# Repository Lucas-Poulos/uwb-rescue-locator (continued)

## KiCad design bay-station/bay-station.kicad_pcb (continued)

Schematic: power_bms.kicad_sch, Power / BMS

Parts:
BT1: 3.7V Li-Ion (JST-PH pigtail); JST_PH_S2B-PH-K_1x02_P2.00mm_Horizontal
C1: 10uF; C_0603_1608Metric
C2, C3: 4.7uF; C_0603_1608Metric
C4: 0.1uF; C_0603_1608Metric
D1: MBRA140T3G; D_SMA
D2, D3: ESD5B5.0ST1G; D_SOD-523
J1: CUI PJ-063AH; BarrelJack_CUI_PJ-063AH_Horizontal
J2: USB4125-GF-A; USB_C_Receptacle_GCT_USB4125-xx-x_6P_TopMnt_Horizontal
Q1: AO3401A; SOT-23
R1: 100k; R_0603_1608Metric
R2: 2.00k; R_0603_1608Metric
R3: 20.0k; R_0603_1608Metric
R4: 330k; R_0603_1608Metric
R5: 110k; R_0603_1608Metric
R6, R7: 5.1k; R_0603_1608Metric
TH1: 10k NTC; R_0603_1608Metric
TP415: VBATT_PROT; TestPoint_Pad_D1.0mm
TP416: THERM; TestPoint_Pad_D1.0mm
TP417: BATT_RAW; TestPoint_Pad_D1.0mm
U1: MCP73871; QFN-20-1EP_4x4mm_P0.5mm_EP2.5x2.5mm
U2: MAX17048G+T10; MAX17048_TDFN8-EP_PLACEHOLDER

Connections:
+5V_IN: C1.1, D1.1 (K), D2.1 (A1), J2.A9 (VBUS), J2.B9 (VBUS), R4.1, U1.3 (SEL), U1.9 (~TE), U1.17 (CE), U1.18 (IN), U1.19 (IN); also elsewhere on the board
+VSYS: C2.1, U1.1 (OUT), U1.20 (OUT); also elsewhere on the board
BARREL_VIN: D1.2 (A), J1.1
BATT_FET_GATE: Q1.1 (G), R1.1
BATT_RAW: BT1.1 (+), Q1.2 (S), TP417.1 (1_1)
CC1: J2.A5 (CC1), R6.1
CC2: J2.B5 (CC2), R7.1
FG_ALRT: U2.5 (~ALRT); also elsewhere on the board
GND: BT1.2 (-), C1.2, C2.2, C3.2, C4.2, D2.2 (A2), D3.2 (A2), J1.2, J2.A12 (GND), J2.B12 (GND), J2.S1 (SHIELD), R1.2, R2.2, R3.2, R5.2, R6.2, R7.2, TH1.2, U1.4 (PROG2), U1.10 (V_{SS}), U1.11 (V_{SS}), U1.21 (V_{SS}), U2.1 (CTG), U2.4 (GND), U2.6 (QSTRT), U2.9 (GND); also elsewhere on the board
I2C_SCL: U2.7 (SCL); also elsewhere on the board
I2C_SDA: U2.8 (SDA); also elsewhere on the board
PROG1: R2.1, U1.13 (PROG1)
PROG3: R3.1, U1.12 (PROG3)
THERM: TH1.1, TP416.1 (1_1), U1.5 (THERM)
VBATT_PROT: C3.1, C4.1, D3.1 (A1), Q1.3 (D), TP415.1 (1_1), U1.14 (V_{BAT}), U1.15 (V_{BAT}), U1.16 (V_{BAT_SENSE}), U2.3 (VDD)
VPCC: R4.2, R5.1, U1.2 (VPCC)
nPG: U1.6 (~PG); also elsewhere on the board
nSTAT1_LBO: U1.8 (STAT1/~LBO); also elsewhere on the board
nSTAT2: U1.7 (STAT2); also elsewhere on the board

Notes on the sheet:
Test pads TP415-TP417 (TP414 +5V_IN deleted 2026-11-18: duplicate of TP104) and the THERM window (2026-11-17, power agent) TH1 sizing, MCP73871 DS20002090E Sec 1.0: ITHERM 47/50/53 uA, VT1 1.20/1.24/1.26 V, VT2 0.23/0.25/0.27 V. Charging is suspended when R_NTC > VT1/ITHERM = 22.6-26.8k (cold) or <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

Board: 4 copper layers, 360 parts (0 on the bottom side), 207 nets, no tracks yet.

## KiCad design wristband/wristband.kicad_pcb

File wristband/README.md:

# Wristband

The worn tag. Open `wristband.kicad_pro` in KiCad.

## Scope

Deliberately minimal: **battery management plus one UWB module, and not much
else.** The tag's only job is to take part in a two-way ranging exchange with
the bay station's center anchor. Everything not needed for that is gone.

- **UWB + MCU**: Qorvo **DWM3001C** (resolved 2026-09-19) -- one module
  containing the DW3110 UWB transceiver, a Nordic nRF52833 MCU, an ST
  LIS2DH12 accelerometer, the UWB and Bluetooth antennas, power management
  and the 38.4 MHz crystal. Its datasheet states it *"requires no RF design
  as the antenna and associated analog and RF components are on the module"*.
- **BLE and the accelerometer are unused.** The tag talks only over UWB. Both
  are silicon inside a module bought for its Cortex-M4 and its UWB radio --
  they cost nothing to leave idle: no external parts, no wiring, no firmware.
  See "Worth revisiting" below.
- **BMS**: sized for "just enough" runtime -- size and weight take priority
  over battery life here, in contrast with the bay station.

Why the tag transmits once per fix: the bay station's center anchor completes
the ranging exchange, and the three outer anchors timestamp that *same*
transmission. One transmission, four measurements -- deliberately, because
the tag is the power-constrained side. See `../docs/positioning.md`.

## Status

Seven hierarchical sheets, all registered in `wristband.kicad_pro`'s `sheets`
list and wired into `wristband.kicad_sch` as sheet symbols.

| Sheet | Status | Contents |
|---|---|---|
| `power_bms` | **Wired** (global labels, no drawn wires), ERC clean | Full battery/charging/protection chain |
| `radio_mcu` | **Wired**, ERC clean | DWM3001C (U4) + decoupling; SWD, RESET_N, SWO, VBAT_SENSE, SOS button, LED_SYS, FW_MARKER |
| `regulation` | **Wired**, ERC clean | TPS7A0233PDBVR LDO -> 3.3V (U5) |
| `programming_debug` | **Wired**, ERC clean | ARM Cortex Debug SWD header |
| `indicators` | **Wired** (global labels + short wires), ERC clean | System LED D4/R13 on P0.14. Charge LED is D2/R10 on `power_bms` |
| `testpoints` | **Wired** (global labels, no drawn wires), ERC clean | TP1-TP5: +3V3, VBAT, 2x GND, FW_MARKER |
| `mechanical` | No wiring needed | 4x M2 mounting holes |

**Every sheet that has nets is now wired.** `mechanical` carries only
mounting holes and needs no nets. `indicators` and `testpoints` were the last
two placement-only sheets (wired 2026-11-18); they used to account for all 13
of the board's `pin_not_connected` ERC errors.

**ERC, re-run 2026-11-18 with kicad-cli 10.0.5 on `wristband.kicad_sch`
(full hierarchy, 39 BOM lines): 2 violations, 0 errors**, both
`lib_symbol_mismatch` warnings from the embedded 8.0-format symbol copies
differing from the 10.x libraries (pre-existing and by design -- see the
flattened-copy workaround in `../CLAUDE.md`). Before: 16 (13 errors).
Per-sheet ERC of a single child sheet shows spurious `isolated_pin_label` /
`power_pin_not_driven` items because the other end of each global label is on
another sheet; run ERC on the root.

**Reference-designator collision fixed 2026-11-18.** `indicators` had its own
`D2`/`R10`/`D3`/`R11`, colliding with `power_bms` (D2 + R10 are the charge LED,
D3 is the VBUS TVS) and `radio_mcu` (R11 is a battery-sense divider resistor);
the BOM export was merging them into rows like `D3 "ESD5B5.0ST1G,LED"`. The
duplicate charge-LED pair was deleted from `indicators` and the system LED
renumbered `D4`/`R13`. The PCB has not been updated from the schematic: it
holds no footprints for `D4`, `R13` or `TP1`-`TP5` yet.

**DRC, re-run 2026-11-06: 210 violations.** This line also used to say "one
violation, `invalid_outline`, because no board outline is drawn yet" --
stale since PR #5 landed the actual PCB (36 footprints, a real outline).
Current breakdown: 100 unconnected_items (the unrouted ratsnest -- expected,
nothing is routed yet), 91 silk_over_copper, 71 silk_overlap, 33
via_dangling, 10 copper_edge_clearance, 3 silk_edge_clearance, 2 clearance.
The silk_over_copper/silk_overlap counts jumped from 57/7 on 2026-11-06 when
every footprint's Value was moved from hidden-on-F.Fab to visible on
F.SilkS (see `docs/decisions.md`) -- expected and accepted: 0402/0603
passive values often don't fit silkscreen cleanly, and resolving the
overlaps is layout work, not a reason to hide the values again.

### Sheet detail

- **`power_bms.kicad_sch`** -- the complete battery chain: 2-pin JST-PH
  battery input (`BT1`); AO3401A P-MOSFET reverse-polarity "ideal diode"
  (`Q1`, `R1`); battery-rail TVS ESD5B5.0ST1G (`D1`); DW01A + FS8205A
  single-cell overcharge/overdischarge/overcurrent protection wired per
  Fortune Semiconductor's own DW01A typical application circuit (`U1`, `Q2`,
  `R2`, `R3`, `C1`); MCP73831 Li-Po charger with power-only USB-C input, PROG
  resistor sized for ~147mA charge current, and datasheet-recommended
  input/output caps (`U2`, `J1`, `R4`, `C2`, `C3`, `R5`, `R6`); bulk/bypass
  decoupling on the protected `VBAT` rail (`C4`, `C5`).

  Net identity is carried entirely by global labels placed on top of each
  pin. ERC: 0 errors, 1 harmless documented warning. Full rationale in
  `power_bms_notes.md`.

- **`radio_mcu.kicad_sch`** -- one `wristband:DWM3001C` (`U4`) plus VDD
  decoupling (`C6` 100nF, `C7` 10uF). Now wired: SWD (`SWDCLK`/`SWDIO`/
  `SWO`), `RESET_N`, `VBAT_SENSE` on P0.02/AIN0, the SOS button on
  P0.17, `LED_SYS` on P0.14 and `FW_MARKER` on P0.22. 14 of the module's 48 pins are tied (adding `LED_SYS` on P0.14 and `FW_MARKER` on P0.22); the rest await the pin
  assignments still open in `../docs/decisions.md`.

  Pin data verified against the real Qorvo DWM3001C Data Sheet Rev B (May
  2022), Table 2. One caveat carried in the symbol: **pin 18 is not
  documented in that table** (it lists 1-17 and 19-48), so it is modelled as
  a passive NC and needs confirming against the land-pattern figure.

  Decoupling values are conservative standard practice, *not*
  datasheet-specified -- the module has on-board power management and Qorvo
  publishes no external application circuit for it.

  Two real layout requirements are recorded in the sheet's own notes: the
  **10 mm antenna keep-out** (Section 7.1) and **keeping the module at least
  1 cm from the PCB edge** (Section 7.2), which reduces the horizontally
  polarized radiation component and improves multipath resilience.

- **`regulation.kicad_sch`** -- TI **TPS7A0233PDBVR** LDO (`U5`, SOT-23-5,
  3.3V fixed, 200mA, 25nA typ Iq) steps the protected `VBAT` rail (up to
  4.2V at full charge) down to `+3V3`. Replaced the MCP1700T-3302E/TT on
  2026-09-23, whose 1.6uA Iq had become the board's largest standby draw --
  see `../docs/decisions.md`. Still required: the DWM3001C's operating
  maximum is 3.6V (Table 4), well under a full battery. **EN must be tied
  high**; the part is disabled when EN floats. See `regulation_notes.md`.

- **`programming_debug.kicad_sch`** -- ARM Cortex Debug SWD connector (`J3`,
  `Connector:Conn_ARM_JTAG_SWD_10`, 2x5 1.27mm). Now targets the nRF52833
  inside U4, via `SWD_CLK` (pin 2) and `SWD_DIO` (pin 3), plus `SWO` (U4 pin 28) and `RESET_N` (pin 47).

- **`indicators.kicad_sch`** -- one system-status LED: `LED_SYS` (U4 pin 7,
  P0.14) -> `R13` 1k -> `D4` -> `GND`, active high. At 3.3 V and a typical
  ~2 V forward drop that is about 1.2 mA. **Unverified:** the nRF52833's
  per-pin drive strength -- the Product Specification was not available
  and Qorvo DS Rev B Table 5 gives drive current only for the DW3110 pins
  (0.8 mA). The charge LED is **not** here: `D2`/`R10` on `power_bms` already
  wire VBUS -> R10 -> D2 -> `CHG_STAT` (MCP73831 STAT, U2 pin 1), the
  topology of Microchip DS20001984H Figure 6-1. STAT is tri-state (Table
  5-1: low while charging, high at charge complete, Hi-Z with no
  battery/shutdown; VOL 1 V max at 4 mA, Section 1.0). At complete, STAT
  sits at VDD-0.4 V to VDD-1 V (VOH), leaving at most ~1 V across LED + R10,
  below a green LED's forward drop, so the LED goes dark. Firmware should
  pulse `D4`, not hold it on.

- **`testpoints.kicad_sch`** -- `TP1` `+3V3`, `TP2` `VBAT`, `TP3`/`TP4` `GND`,
  `TP5` `FW_MARKER` = U4 pin 8 (P0.22), a firmware timing marker so tag-side
  exchange timing is visible on a scope. Each pad sits on a global label.
  Deliberately minimal: the DWM3001C's internals are unreachable and SWD
  already comes out on `J3`. `TP2` matters because there is no power switch
  -- it is the only way to check the battery chain without disconnecting the
  cell. No 0R links: nothing on this sheet shares a net with a path where a
  probe stub could matter.

- **`mechanical.kicad_sch`** -- 4x M2 mounting holes (`H1`-`H4`).

### Next up

1. **Update the PCB's U4 footprint.** The footprint library now holds
   `Qorvo_DWM3001C_Module_19.13x27.1mm_48Pad` (2026-11-18, from Qorvo's own
   Altium library; pad names 1-48 match the symbol), and the schematic points
   at it, but `wristband.kicad_pcb` still embeds the old placeholder -- run
   *Update PCB from Schematic* with footprints replaced. D4, R13 and TP1-TP5 have no
   PCB footprints yet either.
2. ~~Wire the placement-only sheets~~ -- done 2026-11-18. There is no
   MCU-to-transceiver SPI to wire; that link is inside the module. Next: sync
   the PCB from the schematic.

### Worth revisiting

**Motion-gating the UWB.** The LIS2DH12 accelerometer inside the DWM3001C is
unused, but the tag is the power-constrained side of the whole system. Only
ranging when the wearer actually moves is the largest battery lever
available. Worth doing once basic ranging works.

An external IMU was proposed on 2026-09-28 and **rejected** -- the module
already carries an accelerometer, and adding a second one costs board area
and standby current on the one board that can least afford either. See
`../docs/decisions.md`. The one thing the LIS2DH12 cannot give you is
**angular rate**; if a gyro is ever genuinely required, that is a real gap
and reopens the question.

**One assumption here needs checking before anyone calls this free.** The
earlier wording said motion-gating "costs nothing in hardware". That is not
yet established. `I2C0_SDA` (pin 14) and `I2C0_SCL` (pin 15) are brought out
as module pins and are **unconnected in this schematic** -- a netlist export
confirms both sit on `unconnected-(...)` nets. Whether the LIS2DH12 is
reachable with no external parts depends on whether Qorvo fitted pull-ups
*inside* the module:

- If internal pull-ups exist, motion-gating really is firmware-only.
- If not, the bus needs two external pull-ups to `+3V3`, and "costs nothing
  in hardware" is wrong.

I2C is open-drain and cannot return to a logic high without a pull-up
somewhere, so one of those two must be true. Resolve it against the real
**DWM3001C Data Sheet Rev B (May 2022)** -- the same document the symbol in
`libs/` was authored from -- before planning firmware around it.

## Libraries

- `libs/` -- wristband-only symbols/footprints, including the hand-authored
  `DWM3001C` symbol
- `../shared/` -- still registered via `fp-lib-table`/`sym-lib-table`, but
  this board no longer uses anything from it (see `../shared/README.md`)

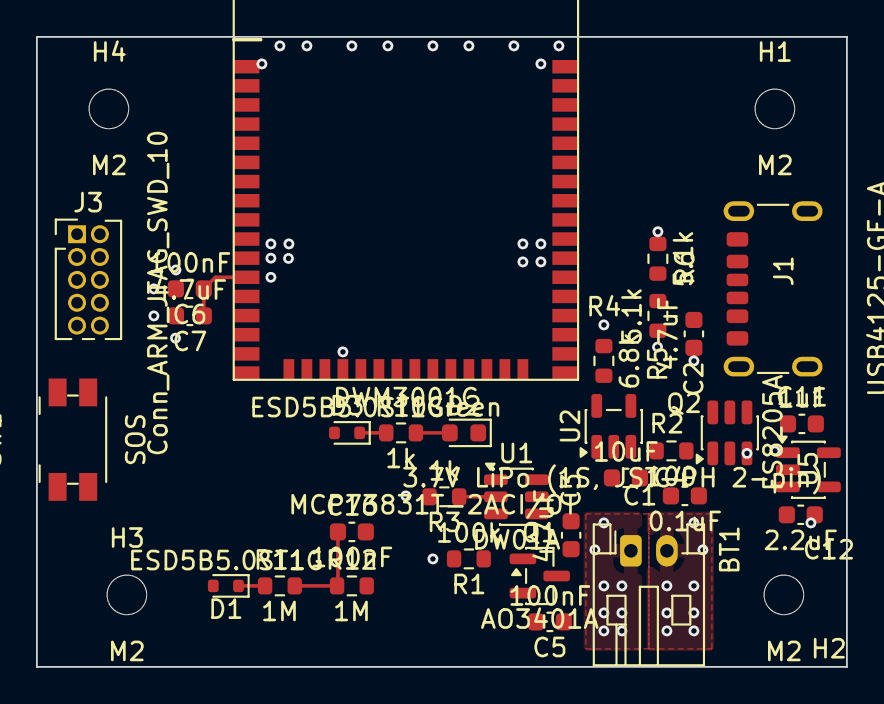
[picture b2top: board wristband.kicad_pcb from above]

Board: 4 copper layers, 45.0 x 35.0 mm, 36 parts (0 on the bottom side), 23 nets.

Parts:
BT1: 3.7V LiPo (1S, JST-PH 2-pin); JST_PH_S2B-PH-K_1x02_P2.00mm_Horizontal
C1: 0.1uF; C_0603_1608Metric
C2, C3, C7: 4.7uF; C_0603_1608Metric
C4: 10uF; C_0603_1608Metric
C5, C6, C16: 100nF; C_0603_1608Metric
C11: 1uF; C_0603_1608Metric
C12: 2.2uF; C_0603_1608Metric
D1, D3: ESD5B5.0ST1G; D_SOD-523
D2: Green; LED_0603_1608Metric
H1, H2, H3, H4: M2; MountingHole_2.2mm_M2
J1: USB4125-GF-A; USB_C_Receptacle_GCT_USB4125-xx-x_6P_TopMnt_Horizontal
J3: Conn_ARM_JTAG_SWD_10; PinHeader_2x05_P1.27mm_Vertical
Q1: AO3401A; SOT-23
Q2: FS8205A; SOT-23-6
R1: 100k; R_0603_1608Metric
R2: 100; R_0603_1608Metric
R3, R10: 1k; R_0603_1608Metric
R4: 6.8k; R_0603_1608Metric
R5, R6: 5.1k; R_0603_1608Metric
R11, R12: 1M; R_0603_1608Metric
SW1: SOS; Panasonic_EVQPUJ_EVQPUA
U1: DW01A; SOT-23-6
U2: MCP73831T-2ACI/OT; SOT-23-5
U4: DWM3001C; DWM3001C_PLACEHOLDER
U5: TPS7A0233PDBVR; SOT-23-5

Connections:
+3V3: C6.1, C7.1, C12.1, J3.1 (VTref), U4.12 (VDD), U5.5 (OUT)
/Radio MCU/SOS_BNT: SW1.1, U4.6 (P0.17)
CC1: J1.A5 (CC1), R5.1
CC2: J1.B5 (CC2), R6.1
CELL_N: BT1.2 (-), C1.2, Q2.1 (S1), U1.4 (TD), U1.6 (GND)
CELL_P: BT1.1 (+), Q1.2 (S)
CHG_PROG: R4.1, U2.5 (PROG)
CHG_STAT: D2.1 (K), U2.1 (STAT)
DW01A_VCC: C1.1, R2.2, U1.5 (VCC)
FS_D12: Q2.2 (D12), Q2.5 (D12)
GND: C2.2, C3.2, C4.2, C5.2, C6.2, C7.2, C11.2, C12.2, C16.2, D1.2 (A2), D3.2 (A2), J1.A12 (GND), J1.B12 (GND), J1.SH (SHIELD), J3.3 (GND), J3.5 (GND), J3.9 (GNDDetect), Q2.3 (S2), R1.2, R3.2, R4.2, R5.2, R6.2, R12.2, SW1.2, U2.2 (VSS), U4.1 (GND), U4.11 (GND), U4.21 (GND), U4.38 (GND), U4.48 (GND), U5.2 (GND)
unnamed: D2.2 (A), R10.2
PROT_CS: R3.1, U1.2 (CS)
PROT_OC: Q2.4 (G2), U1.3 (OC)
PROT_OD: Q2.6 (G1), U1.1 (OD)
Q1_GATE: Q1.1 (G), R1.1
RESET_N: J3.10 (~RESET), U4.47 (RESET)
SWDCLK: J3.4 (SWCLK/TCK), U4.2 (SWD_CLK)
SWDIO: J3.2 (SWDIO/TMS), U4.3 (SWD_DIO)
SWO: J3.6 (SWO/TDO), U4.28 (P1.00)
VBAT: C3.1, C4.1, C5.1, C11.1, D1.1 (A1), Q1.3 (D), R2.1, R11.1, U2.3 (VBAT), U5.1 (IN), U5.3 (EN)
VBAT_SENSE: C16.1, R11.2, R12.1, U4.46 (P0.02)
VBUS: C2.1, D3.1 (A1), J1.A9 (VBUS), J1.B9 (VBUS), R10.1, U2.4 (VDD)

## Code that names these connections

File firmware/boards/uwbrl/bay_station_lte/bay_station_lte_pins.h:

/*
 * nRF9151 pin map for the bay station -- THE ONE PLACE pins get filled in.
 *
 * Every name below is a net from docs/net-contract.md. The pin each net
 * lands on is decided in exactly one hardware document:
 *     bay-station/connectivity_notes.md, "nRF9151 GPIO allocation"
 * Filled 2026-11-17 from that table, and cross-checked pin by pin against
 * `kicad-cli sch export netlist` of the merged schematic (every nRF9151 GPIO
 * lands on the net named here, some through 0R rework links). If the
 * schematic moves a pin, change it there first, then here. Nothing else in
 * firmware/ names a pin number.
 *
 * The nRF9151 exposes a single GPIO port (gpio0), so these are pin numbers
 * on gpio0 only -- confirm against the nRF9151 Product Specification pin
 * assignment table when filling them in.
 *
 * Included by the .dts (C preprocessor), so: #defines only, no C code.
 */
#ifndef BAY_STATION_LTE_PINS_H_
#define BAY_STATION_LTE_PINS_H_

#define UWBRL_LTE_PINS_ASSIGNED 1

#if !UWBRL_LTE_PINS_ASSIGNED
#error "nRF9151 pins not assigned: fill firmware/boards/uwbrl/bay_station_lte/bay_station_lte_pins.h from bay-station/connectivity_notes.md"
#endif

/* ---- net-contract s2: UWB array, one SPI bus (SPIM3) ------------------- */
#define PIN_UWB_SCK      13      /* P0.13 */
#define PIN_UWB_MOSI     14      /* P0.14 */
#define PIN_UWB_MISO     15      /* P0.15 */
#define PIN_UWB_CS0_N    16      /* P0.16 -- A0 center (TWR). */
#define PIN_UWB_CS1_N    17      /* P0.17 -- A1 outer. */
#define PIN_UWB_CS2_N    18      /* P0.18 -- A2 outer. */
#define PIN_UWB_CS3_N    19      /* P0.19 -- A3 outer. */
#define PIN_UWB_IRQ0     8       /* P0.08 */
#define PIN_UWB_IRQ1     9       /* P0.09 */
#define PIN_UWB_IRQ2     10      /* P0.10 */
#define PIN_UWB_IRQ3     11      /* P0.11 */
#define PIN_UWB_RST_N    12      /* P0.12 -- open-drain, shared. */
#define PIN_UWB_WAKEUP   20      /* P0.20 -- shared. */
#define PIN_UWB_SYNC     21      /* P0.21 -- shared SYNC/OSTR. */

/* ---- net-contract s3: clock ------------------------------------------- */
/* TCXO_EN omitted: the RPT1490LN has no enable pin (clock_dist_notes.md). */
#define HAS_TCXO_EN      0

/* ---- net-contract s4: sensors (TWIM2) --------------------------------- */
#define PIN_I2C_SCL      5       /* P0.05 */
#define PIN_I2C_SDA      6       /* P0.06 */
/* P0.24 is spare since 2026-11-18: the IIS2MDC has one INT/DRDY pin, so MAG_DRDY is gone. */
#define PIN_MAG_INT      25      /* P0.25 -- IIS2MDC INT/DRDY */
#define PIN_ACC_INT1     7       /* P0.07 */
#define PIN_ACC_INT2     26      /* P0.26 */
#define PIN_FG_ALRT      27      /* P0.27 */

/*
 * 7-bit I2C addresses. Set by address-strap pins on the orientation sheet,
 * not by firmware. Values per datasheet once the strap is known:
 *   IIS2MDC:  0x1E, fixed (no address pin)
 *             -- ST DocID030986 Rev 1, Table 21 (default address 0011110b)
 *   IIS2DLPC: 0x18 (SA0 = GND) or 0x19 (SA0 = VDD)
 *             -- ST DocID031788 Rev 4, "SAD associated to the IIS2DLPC is 001100xb"
 *   MAX17048: 0x36 fixed -- Maxim 19-6171 Rev 7, "Slave Address"
 */
/* Devicetree needs each address twice: as a cell (0x..) and as the node's
 * unit address (bare hex). Keep each pair in step. */
#define I2C_ADDR_IIS2MDC  0x1e /* fixed */
#define I2C_UNIT_IIS2MDC  1e
#define I2C_ADDR_IIS2DLPC 0x19 /* SA0 -> Vdd_IO via R414 (orientation sheet) */
#define I2C_UNIT_IIS2DLPC 19
#define I2C_ADDR_MAX17048 0x36 /* fixed, 19-6171 Rev 7 "Slave Address" 0110110 (io handoff) */
#define I2C_UNIT_MAX17048 36

/* ---- net-contract s5: BLE bridge (UARTE1) ----------------------------- */
#define PIN_BRIDGE_TXD   0       /* P0.00 -- nRF9151 TX -> BT840 RX. */
#define PIN_BRIDGE_RXD   1       /* P0.01 */
#define PIN_BRIDGE_RTS   2       /* P0.02 */
#define PIN_BRIDGE_CTS   3       /* P0.03 */
#define PIN_BRIDGE_IRQ   4       /* P0.04 -- BT840 -> nRF9151. */
#define PIN_RESET_BLE_N  28      /* P0.28 -- open-drain. */

/* ---- net-contract s6: debug (UARTE0 = shell/log) ---------------------- */
#define PIN_DBG_UART_TX  22      /* P0.22 */
#define PIN_DBG_UART_RX  23      /* P0.23 */
#define PIN_BTN_USER     29      /* P0.29 -- active low. */

/* ---- net-contract s7: status ------------------------------------------ */
#define PIN_LED_SYS      30      /* P0.30 */
#define PIN_LED_LTE      31      /* P0.31 */
/* MCP73871 status: LEDs only, never a GPIO -- all 32 GPIOs are used, and the
 * open-drain LED nodes idle near +VSYS (connectivity_notes.md s2). */
#define HAS_CHG_STATUS   0

/* LED polarity depends on the indicators sheet (sink vs source). */
#define LED_ACTIVE_FLAGS GPIO_ACTIVE_HIGH /* GPIO sources ~1.1 mA via 1.2k (indicators.kicad_sch) */

#endif /* BAY_STATION_LTE_PINS_H_ */

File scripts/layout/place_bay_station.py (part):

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

POLISH_PASSES = 6
RF_NET = re.compile(r"LTE_RF_PIN|LTE_ANT|GNSS_RF|GNSS_ANT$|GNSS_LNA_A|GNSS_LNA_IN")
LARGE_NET = 9        # nets with more pads than this are costed by nearest-pad distance, not MST
# clock tree parts (precision-critical, positioned by the constructive pass) are not polished
POLISH_SKIP = {"R230", "R231", "R232", "R233", "R234", "C24", "C25", "C26", "C27", "C210", "C211", "C212", "C213", "C214"}
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    for n in range(4):
        cx, cy, rot = SLOT[n]
        fixed["U%d" % (4 + n)] = (cx, cy, rot)
        # SMA at the board edge, pad 1 on the RF1 pin x
        if rot == 0:
            fixed["J%d" % (20 + n)] = (cx + 1.0, H, 180)
        else:
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    """RF chain from DW3210 RF1 to the SMA: identical template for all four anchors."""
    cx, cy, rot = SLOT[n]
    s = 1.0 if rot == 0 else -1.0       # +1: chain runs south, -1: runs north
    xl = cx + (1.0 if rot == 0 else -1.0)  # RF1 pin x
    vr = 270 if rot == 0 else 90      # vertical series parts: pad 1 toward the chip
    pos = {}
    pos["C%d" % (47 + 8 * n)] = (xl, cy + s * 4.25, vr)           # 2.0 pF series, at the pin
    pos["C%d" % (200 + 2 * n)] = (xl + s * 1.75, cy + s * 5.5, 0 if rot == 0 else 180)   # DNP pi shunt A
    pos["R%d" % (220 + n)] = (xl, cy + s * 6.5, vr)             # 0R pi series
    pos["C%d" % (201 + 2 * n)] = (xl + s * 1.75, cy + s * 7.75, 0 if rot == 0 else 180)    # DNP pi shunt B at the SMA
    # RF2 termination 49R9 under pin 13 (x - 1.0 of centre => mirrored for rot 180)
    x13 = cx - 1.0 if rot == 0 else cx + 1.0
    pos["R%d" % (33 + n)] = (x13, cy + s * 4.25, vr)
    return pos
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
